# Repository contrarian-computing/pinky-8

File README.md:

# PINKY-8

An affordable, 6502-based SBC for education and retrocomputing that you can build yourself

Note: The image above is of the earlier Revision A board. Revision B has similar dimensions, additional buttons and jumpers, and an improved layout permitting typical corner mounting holes.

When ARM is too much, try PINKY.

Note: The following refers to the Rev B board tag.

## Overview
* Uses WDC's updated version of the venerable 6502 8-bit microprocessor for authentic retrocomputing
* 32K of addressable SRAM
* 128K of Flash ROM in 8 jumper-selected, 16K banks
* W65C22S Versatile Interface Adapter supplying 2 x 8-bit bi-directional GPIOs with control lines
* Power-on reset as well as manual reset via push button
* NMI button facilitates debugging and custom functionality
* USB-B receptacle for 5V power, works with any well-regulated phone charger
* Compact 3.5" x 2.8" form-factor
* Uses only through-hole components for easy hand assembly
* Two-sided PCB and minimal componentry make for extremely affordable retrocomputing

## Design Approach

### Period Appropriate with New Components
PINKY-8 is intended as an affordable educational and/or hobbyist device for those wishing to gain firsthand experience
with the historically significant 6502 processor and vintage computer construction. As such, PINKY-8 incorporates chips
still in production today that are similar to those found in commercial designs of the late 1970s and early 1980s. 
Building a PINKY-8 does not require scavenging parts from vintage machines and every bit can easily be soldered by hand.

### Minimal but Expandable
PINKY-8 is a barebones SBC with onboard I/O limited to the 2 x 8-bit bi-directional GPIO pins and control lines offered by
the 65C22S Versatile Interface Adapter. These are exposed in two 2x7 socket headers into which expansion boards supporting
other forms of I/O (e.g. SPI, I2C, video, sound) can be plugged, similar to Arduino shields. There is no elaborate
programmable bank switching for RAM or ROM, just jumpers on the board. In lieu of power regulation circuitry, PINKY-8 depends on a well-regulated 5V supply (such as a phone charger) attached via a standard USB A-to-B cable.

### Fully Open-Source
PINKY-8 is open-source hardware created with open-source hardware, specifically KiCad 4.0.6. Source for its ROM is located in a separate repository and can be assembled with the open-source CC65 suite.

## Specifications

### Memory Map
For good performance at minimal cost, address decoding is performed using a single 74AC00 Quad NAND Gate using a
scheme advanced by 6502 afficionado, Garth Wilson.

SRAM: $0000-$7FFF (32K)  
VIA:  $8000-$800F  
ROM:  $C000-$FFFF (16K)  

### Clock
Components have been selected to support a maximum clock speed of about 5Mhz. Beyond that faster ROM and RAM are 
necessary which will considerably increase the cost of a complete board. To approach the W65C02S's 14Mhz maximum
rated speed requires very fast RAM into which program data is typically copied from slower ROM at boot by means
of still more componentry.

### PCB
The board has standard-width traces and drill holes on a two-sided design to facilitate affordable manufacturing by nearly
any boardhouse.

## Bill of Materials

### Required
1 x W65C02S, PDIP-40  
1 x W65C22S, PDIP-40  
1 x SST39SF010A-70, PDIP-32  
1 x AS6C62256-55PCN, PDIP-28  
1 x SN74AC00N, PDIP-14  
1 x 1-5Mhz 50% Duty Cycle, 10ns Rise Time Oscillator, DIP-8  
2 x DS1813-5+ (5% Tolerance), TO-92-3 w/Bent Legs  
2 x Tactile Switch 6.0x6.0x4.3mm, Through Hole, 4 Lead  
1 x USB B Female Through-Hole Receptacle  
6 x 0.1uF 50V MLCC Axial Capacitors  
3 x 3.3kOhm 1/4W Axial Metal Film Resistors  
1 x 100uF 10V Radial Aluminum Electrolytic Capacitor  
3 x 1x3 Pin Header .1" spacing  
2 x 2x7 Female Socket Header .1" spacing (can substitute with pin header)  
3 x 2-pin Jumper / Shunt, .1" spacing

### Optional
2 x DIP-40 Dual wipe or machined sockets  
1 x DIP-32 Dual wipe or machined socket  
1 x DIP-28 Dual wipe or machined socket  
1 x DIP-14 Dual wipe or machined socket  
1 x DIP-8 Dual wipe or machined socket  
4 x M2.5 standoffs for mounting

## Construction

Detailed instructions for board assembly will be added to the wiki in time.

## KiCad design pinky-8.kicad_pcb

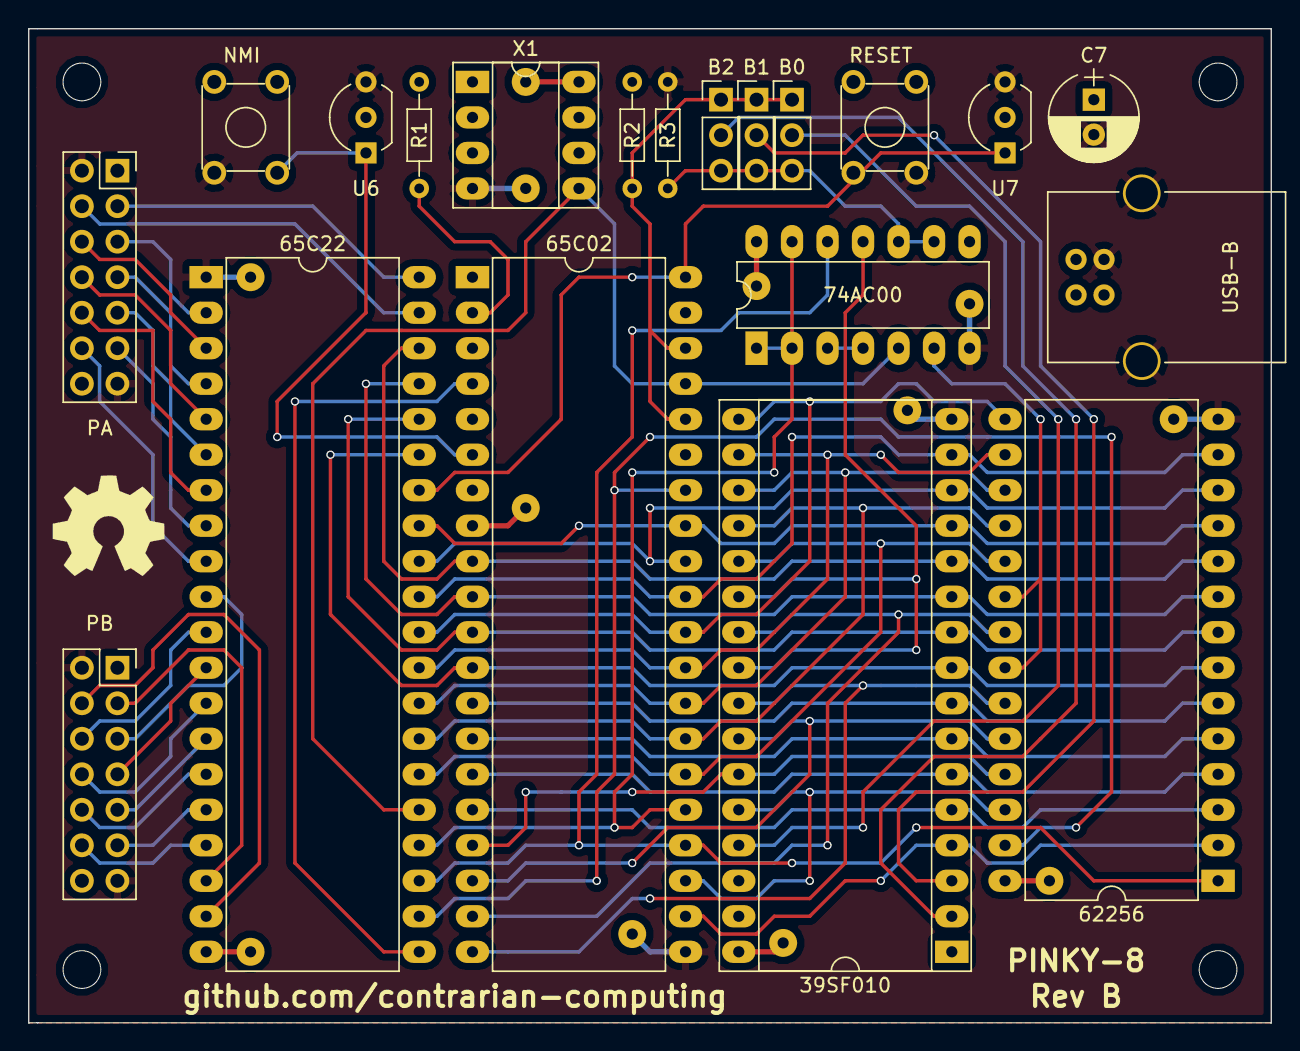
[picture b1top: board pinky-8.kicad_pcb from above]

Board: 2 copper layers, 88.9 x 71.1 mm, 32 parts (0 on the bottom side), 60 nets.

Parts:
39SF010: GLS29EE010; DIP-32_W15.24mm_Socket_LongPads
65C02: W65C02S; DIP-40_W15.24mm_LongPads
65C22: W65C22S; DIP-40_W15.24mm_LongPads
74AC00: 74AC00; DIP-14_W7.62mm_LongPads
62256: AS6C62256; DIP-28_W15.24mm_LongPads
B0, B1, B2: CONN_01X03; Pin_Header_Straight_1x03_Pitch2.54mm
C7: 100uF; CP_Radial_D6.3mm_P2.50mm
NMI: SW_Push_Dual; SW_TH_Tactile_Omron_B3F-10xx
P1, P2, P3, P4, P5, P6, P10, P11, P13, P14, P15, P17: CONN_01X01; SolderWirePad_single_0-8mmDrill
PA: PERIPHERAL A; Socket_Strip_Straight_2x07_Pitch2.54mm
PB: PERIPHERAL B; Socket_Strip_Straight_2x07_Pitch2.54mm
R1, R2, R3: 3.3K; R_Axial_DIN0204_L3.6mm_D1.6mm_P7.62mm_Horizontal
RESET: SW_Push_Dual; SW_TH_Tactile_Omron_B3F-10xx
U6, U7: DS1813; TO-92_Inline_Wide
USB-B: USB_B
X1: MXO45; DIP-8_W7.62mm_Socket_LongPads

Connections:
/A0: 39SF010.12, 65C02.9, 65C22.38, 62256.10
/A1: 39SF010.11, 65C02.10, 65C22.37, 62256.9
/A2: 39SF010.10, 65C02.11, 65C22.36, 62256.8
/A3: 39SF010.9, 65C02.12, 65C22.35, 62256.7
/A4: 39SF010.8, 65C02.13, 62256.6
/A5: 39SF010.7, 65C02.14, 62256.5
/A6: 39SF010.6, 65C02.15, 62256.4
/A7: 39SF010.5, 65C02.16, 62256.3
/A8: 39SF010.27, 65C02.17, 62256.25
/A9: 39SF010.26, 65C02.18, 62256.24
/A10: 39SF010.23, 65C02.19, 62256.21
/A11: 39SF010.25, 65C02.20, 62256.23
/A12: 39SF010.4, 65C02.22, 62256.2
/A13: 39SF010.28, 65C02.23, 62256.26
/A14: 65C02.24, 65C22.23, 74AC00.12, 62256.1
/A15: 65C02.25, 65C22.24, 74AC00.1, 74AC00.2, 74AC00.13
/A15#: 74AC00.3, 74AC00.4
/CA1: 65C22.40, PA.3
/CA2: 65C22.39, PA.4
/CB1: 65C22.18, PB.3
/CB2: 65C22.19, PB.4
/CLK: 65C02.37, 65C22.25, 74AC00.5, X1.5
/D0: 39SF010.13, 65C02.33, 65C22.33, 62256.11
/D1: 39SF010.14, 65C02.32, 65C22.32, 62256.12
/D2: 39SF010.15, 65C02.31, 65C22.31, 62256.13
/D3: 39SF010.17, 65C02.30, 65C22.30, 62256.15
/D4: 39SF010.18, 65C02.29, 65C22.29, 62256.16
/D5: 39SF010.19, 65C02.28, 65C22.28, 62256.17
/D6: 39SF010.20, 65C02.27, 65C22.27, 62256.18
/D7: 39SF010.21, 65C02.26, 65C22.26, 62256.19
/IRQ#: 65C02.4, 65C22.21
/NMI#: 65C02.6, NMI.2, U6.1
/PA0: 65C22.2, PA.5
/PA1: 65C22.3, PA.6
/PA2: 65C22.4, PA.7
/PA3: 65C22.5, PA.8
/PA4: 65C22.6, PA.9
/PA5: 65C22.7, PA.10
/PA6: 65C22.8, PA.11
/PA7: 65C22.9, PA.12
/PB0: 65C22.10, PB.5
/PB1: 65C22.11, PB.6
/PB2: 65C22.12, PB.7
/PB3: 65C22.13, PB.8
/PB4: 65C22.14, PB.9
/PB5: 65C22.15, PB.10
/PB6: 65C22.16, PB.11
/PB7: 65C22.17, PB.12
/PLDN: 74AC00.9, 74AC00.10, B0.3, B1.3, B2.3, R3.1
/PLUP: 65C02.36, 65C02.38, B0.1, B1.1, B2.1, R2.1
/RAMSEL#: 74AC00.6, 62256.20, 62256.22
/RB0: 39SF010.29, B0.2
/RB1: 39SF010.3, B1.2
/RB2: 39SF010.2, B2.2
/ROMSEL#: 39SF010.22, 39SF010.24, 74AC00.11
/RST#: 65C02.40, 65C22.34, RESET.4, U7.1
/RW#: 65C02.34, 65C22.22, 62256.27
GND: 39SF010.16, 65C02.21, 65C22.1, 74AC00.7, 62256.14, C7.2, NMI.4, P4.1, P5.1, P6.1, P13.1, P14.1, P17.1, PA.2, PA.13, PB.2, PB.13, R3.2, RESET.2, U6.3, U7.3, USB-B.4, USB-B.5, X1.4
unnamed: 65C02.2, R1.2
VCC: 39SF010.31, 39SF010.32, 65C02.8, 65C22.20, 74AC00.14, 62256.28, C7.1, P1.1, P2.1, P3.1, P10.1, P11.1, P15.1, PA.1, PA.14, PB.1, PB.14, R1.1, R2.2, U6.2, U7.2, USB-B.1, X1.8

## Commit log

2017-06-27 Initial commit of REV A files
2017-06-27 Add MIT License
2017-06-27 Create initial readme
2017-06-27 Adding photo of completed Rev A board.
2017-06-27 Adding completed board image to readme.
2017-07-03 Adding images of the schematic.
2017-07-03 Changing exported schematic to monochrome.
2017-08-15 Updating to Rev B spec.
2017-08-15 Reducing data line trace overlap.
2017-08-25 Finalizing PCB layout and updating schematic.
2019-02-26 Fixing a routing error
2019-03-03 Updating to latest KiCad format
